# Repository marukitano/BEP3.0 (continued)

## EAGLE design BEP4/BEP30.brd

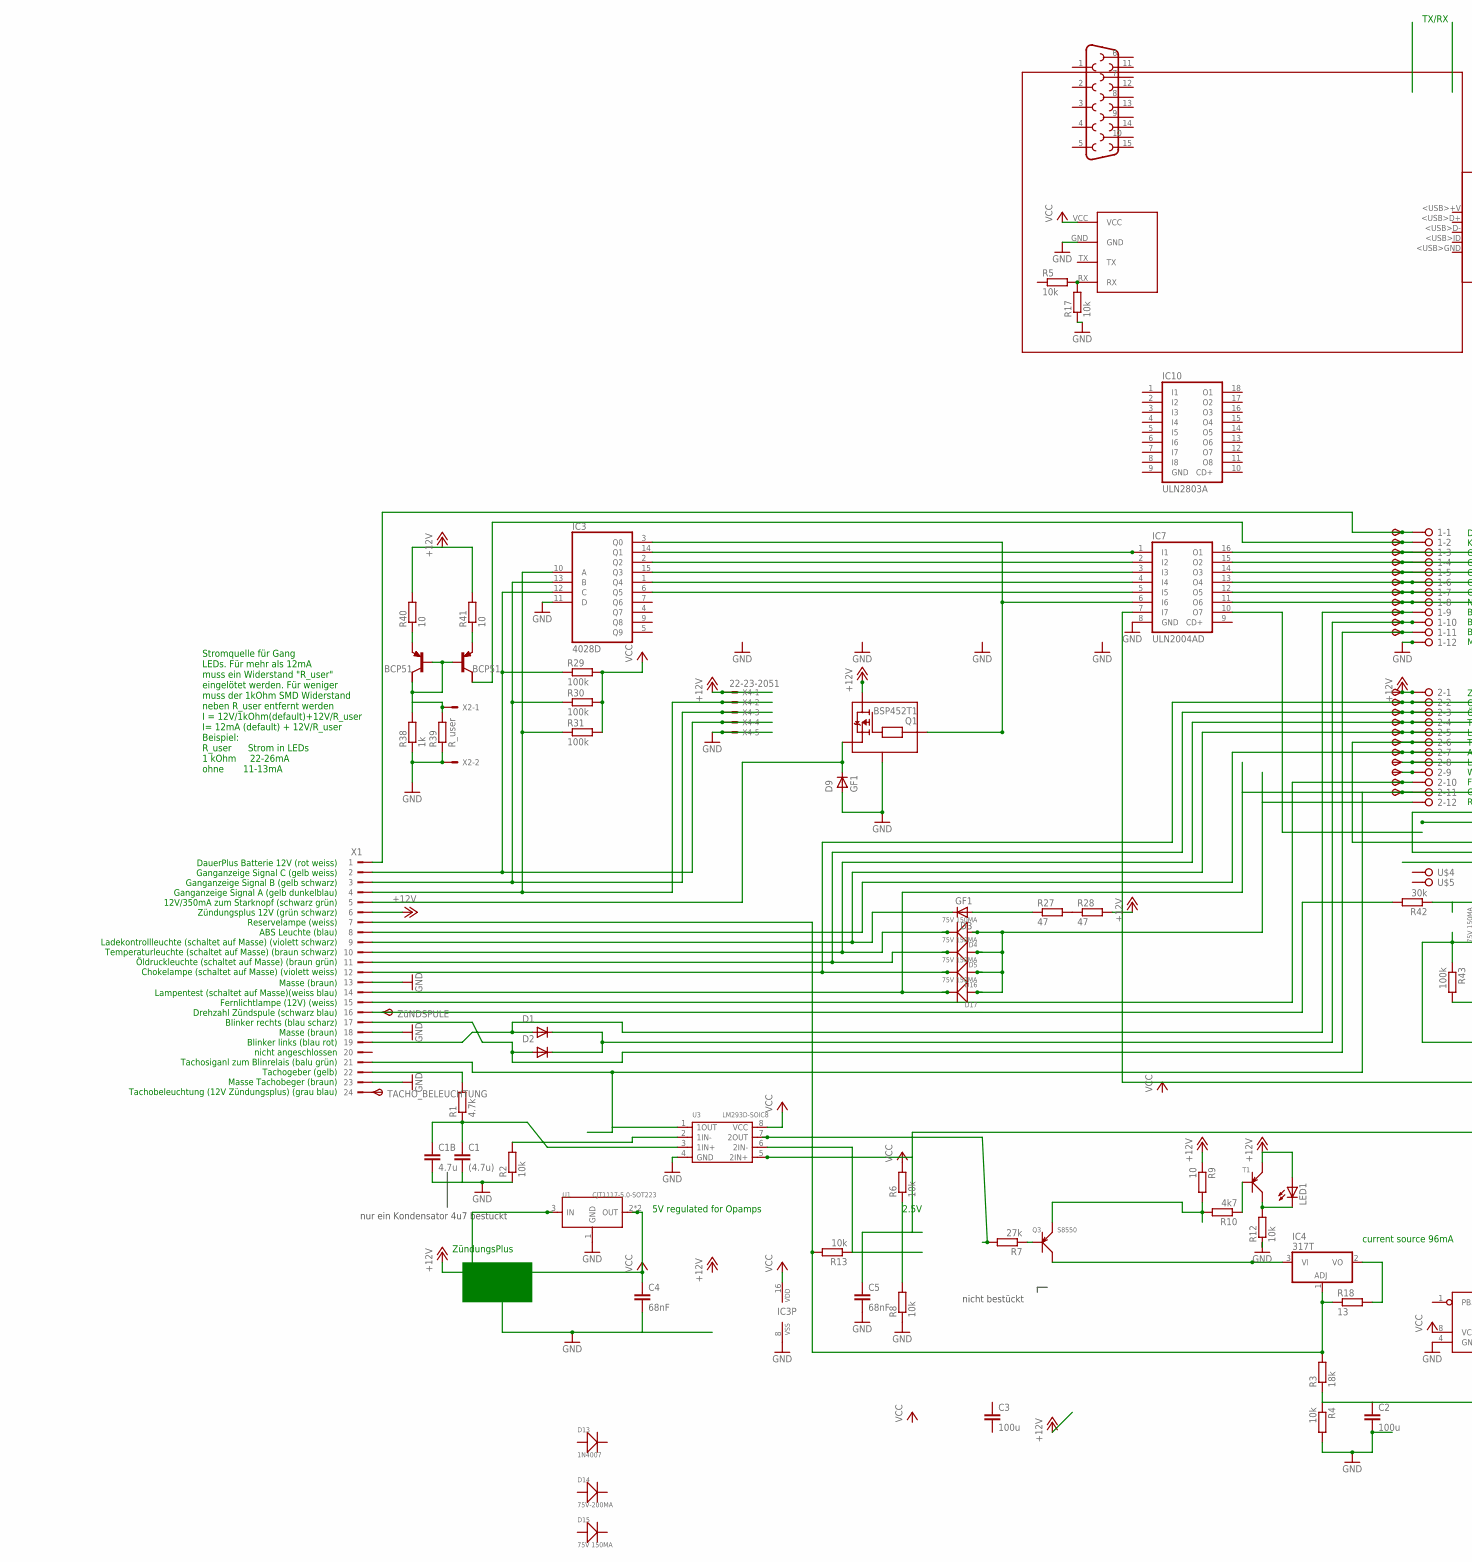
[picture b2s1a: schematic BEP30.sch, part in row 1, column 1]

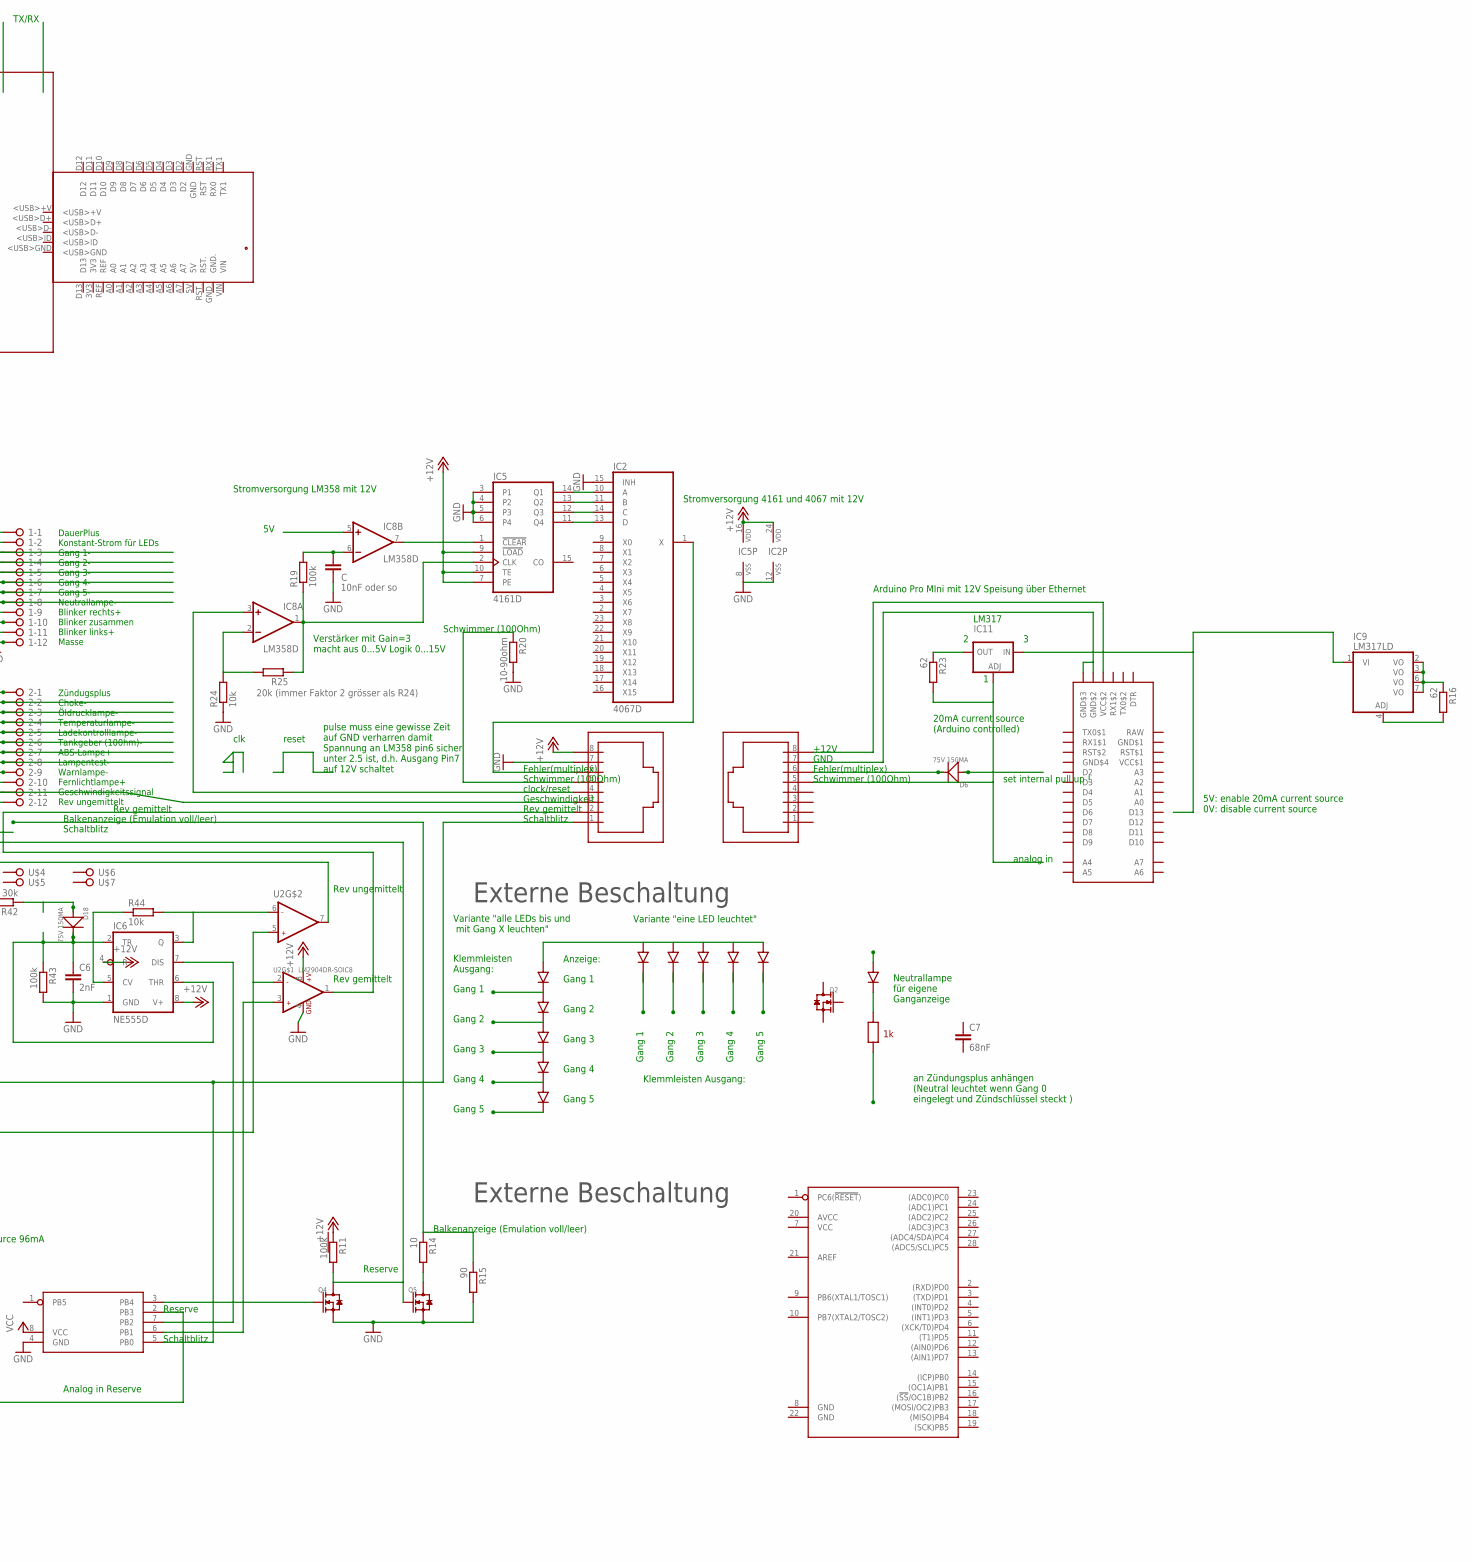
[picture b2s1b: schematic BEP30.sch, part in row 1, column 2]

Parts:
1, 2: 2081-1132; 12-PIN
C: 10nF oder so; C0805K
C1: (4.7u); C1206
C1B: 4.7u; C0805K
C2, C3: 100u; C1206K
C4, C5, C7: 68nF; C1206K
C6: 2nF; C1206K
D1, D2, D3, D9: GF1; SMA-DO214AC
D4, D5, D6, D15, D16, D17, D18: 75V 150MA; LED-1206
D13: 1N4007; DO-214AC
D14: 75V-200MA; LL-34
IC1: ATMEGA328-DIP; DIL28-SLIM
IC2: 4067D; SO24W
IC3: 4028D; SO16
IC4: 317T; TO220H
IC5: 4161D; SO16
IC6: NE555D; SO08
IC7: ULN2004AD; SO16
IC8: LM358D; SO08
IC9: LM317LD; SO08
IC10: ULN2803A; SOP18
IC11: LM317TS; 317TS
J1, J2: RJ45-TE
J_BT_BOARD_1: BLUETOOTH_BOARD; BT_BOARD_FOOTPRINT
LED1: LED3MM
PCB1: ARDUINO_NANO
Q1: BSP452T1; SOT223
Q2, Q4, Q5: SMD-MOSFET-N-CH-50V-200MA-BSS138W-7-F(SOT-23); SOT-23
Q3: S8550; SOT-23
R1: 4.7k; R0805
R2, R4, R5, R6, R8, R12, R13, R17, R24, R44: 10k; R0805
R3: 18k; R0805
R7: 27k; R0805
R9, R14, R40, R41: 10; R0805
R10: 4k7; R0805
R11, R19, R29, R30, R31, R43: 100k; R0805
R15: 90; R0805
R16, R23: 62; R0805
R18: 13; R1206
R20: 10-90ohm; R0805
R25: 20k (immer Faktor 2 grösser als R24); R0805
R27, R28: 47; V235/17
R38: 1k; R0805
R39: R_user; R0805
R42: 30k; R0805
T1: SMD-TRANSISTORS-PNP-25V-500MA-S8550(SOT-23); SOT-23
T13, T14: BCP53T1; SOT223
TACHO_BELEUCHTUNG: TPSP1_1MM; P1_1.0MM
TP1, TP2, TP3, TP4, TP5, TP6, TP7, TP8, TP9, TP10, TP11, TP12, TP16, TP17, TP18, TP19, TP21, TP22, TP23, TP24, TP25, TP26: TPSB1,27; B1,27
U1: CJT1117-5.0-SOT223; SOT-223
U2: LM2904DR-SOIC8; SOIC8-1.27-5X4MM
U3: LM293D-SOIC8; SOIC8-1.27-5X4MM
U$1: TINY85P; DIL08
U$2: DB15
U$3: ARDUINO_PRO_MINI
U$4, U$5, U$6, U$7: 2081-1121; 1-PIN
X1: CON_BMW; 24-PIN
X2: 22-23-2021
X4: 22-23-2051
ZüNDSPULE: TPSP1_1MM; P1_1.0MM

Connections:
+12V: 2.1, IC2.24 (VDD), IC5.7 (PE), IC5.9 (!LOAD), IC5.10 (TE), IC5.16 (VDD), IC6.4 (R), IC6.8 (V+), J1.8, LED1.A, Q1.4 (V+), R9.1, R11.1, R28.2, R40.2, R41.2, T1.2 (E), TP12.TP, U1.3 (IN), U2.8 (+V), X1.6, X4.1
AVCC: IC1.20 (AVCC)
GND: 1.12, C.1, C1.2, C1B.2, C2.2, C4.2, C5.2, C6.2, D9.A, IC1.8 (GND), IC1.22 (GND), IC2.12 (VSS), IC2.15 (INH), IC3.8 (VSS), IC3.11 (D), IC5.3 (P1), IC5.4 (P2), IC5.5 (P3), IC5.6 (P4), IC5.8 (VSS), IC6.1 (GND), IC7.8 (GND), IC10.9 (GND), J1.7, J_BT_BOARD_1.GND, Q1.2 (GND), Q4.2 (S), Q5.2 (S), R2.1, R4.2, R8.1, R12.1, R15.2, R17.1, R20.2, R24.1, R38.1, R39.1, R43.2, U1.1 (GND), U2.4 (GND), U3.4 (GND), U$1.4 (GND), X1.13, X1.18, X1.23, X2.2, X4.5
GND$1: U$3.GDN$1 (GND$1)
GND$4: U$3.GND$4
unnamed: 2.12, D4.+, D5.+, D16.+, D17.+
unnamed: IC3.10 (A), R31.1, X1.4, X4.2
unnamed: IC3.13 (B), R30.1, X1.3, X4.3
unnamed: 2.7, TP22.TP, X1.8
unnamed: IC3.3 (Q0), IC7.6 (I6), Q1.3 (IN)
unnamed: IC3.2 (Q2), IC7.2 (I2)
unnamed: R27.2, R28.1
unnamed: IC4.3 (VI), Q3.3 (C)
unnamed: R13.1, U3.6 (2IN-)
unnamed: D9.K (C), Q1.1 (OUT), X1.5
unnamed: 2.2, D16.-, TP16.TP, X1.12
unnamed: 2.3, D5.-, TP17.TP, X1.11
unnamed: 2.4, D4.-, TP18.TP, X1.10
unnamed: IC4.1 (ADJ), R3.2, R13.2, R18.1, X1.7
unnamed: Q4.1 (G), U$1.3 (PB4)
unnamed: IC3.12 (C), R29.1, X1.2, X4.4
unnamed: 1.5, IC7.14 (O3), TP5.TP
unnamed: D6.-, J2.6
unnamed: 1.9, D1.A, TP9.TP, X1.19
unnamed: 1.11, D2.A, TP11.TP, X1.17
unnamed: 1.10, D1.K (C), D2.K (C), TP10.TP
unnamed: R1.2, X1.22
unnamed: C1.1, C1B.1, R1.1, U3.3 (1IN+)
unnamed: R2.2, U3.2 (1IN-)
unnamed: U3.1 (1OUT), X1.21
unnamed: 1.6, IC7.13 (O4), TP6.TP
unnamed: C2.1, R3.1, R4.1, U$1.2 (PB3)
unnamed: IC4.2 (VO), R18.2
unnamed: C5.1, R6.1, R8.2, U2.2 (-IN1), U2.5 (+IN2), U3.5 (2IN+)
unnamed: R10.1, T1.1 (B)
unnamed: R7.2, U3.7 (2OUT)
unnamed: Q3.1 (B), R7.1
unnamed: J_BT_BOARD_1.RX, R5.2, R17.2
unnamed: IC6.7 (DIS), U$1.7 (PB2)
unnamed: IC3.14 (Q1), IC7.1 (I1)
unnamed: IC3.15 (Q3), IC7.3 (I3)
unnamed: U2.3 (+IN1), U$1.6 (PB1)
unnamed: R14.1, R15.1
unnamed: R42.2, X1.16, ZüNDSPULE.TP
unnamed: IC7.7 (I7), J1.1, U$1.5 (PB0)
unnamed: Q3.2 (E), R9.2, R10.2
unnamed: LED1.K (C), R12.2, T1.3 (C)
unnamed: J1.2, U2.1 (OUT1)
unnamed: Q5.3 (D), R14.2
unnamed: IC3.1 (Q4), IC7.4 (I4)
unnamed: 1.7, IC7.12 (O5), TP7.TP
unnamed: 1.8, IC7.11 (O6), TP8.TP
unnamed: 2.10, TP25.TP, X1.15
unnamed: D3.A, R27.1
unnamed: 2.5, D3.K (C), TP19.TP, X1.9
unnamed: J1.5, R20.1
unnamed: IC2.10 (A), IC5.14 (Q1)
unnamed: TACHO_BELEUCHTUNG.TP, X1.24
unnamed: 1.2, T14.2 (C), TP2.TP
unnamed: 2.6, Q4.3 (D), Q5.1 (G), R11.2, TP21.TP
unnamed: IC9.2 (VO), IC9.3 (VO), IC9.6 (VO), IC9.7 (VO), R16.1
unnamed: IC3.6 (Q5), IC7.5 (I5)
unnamed: IC2.11 (B), IC5.13 (Q2)
unnamed: IC2.14 (C), IC5.12 (Q3)
unnamed: 1.4, IC7.15 (O2), TP4.TP
unnamed: 1.3, IC7.16 (O1), TP3.TP
unnamed: R38.2, R39.2, T13.1 (B), T13.2 (C), T14.1 (B), X2.1
unnamed: 1.1, TP1.TP, X1.1
unnamed: R40.1, T13.3 (E)
unnamed: R41.1, T14.3 (E)
unnamed: D18.+, R42.1
unnamed: IC6.3 (Q), R44.2, U2.6 (-IN2)
unnamed: IC6.5 (CV), R44.1
unnamed: IC2.13 (D), IC5.11 (Q4)
unnamed: IC8.3 (+IN), J1.4
unnamed: C.2, IC8.6 (-IN), R19.2
unnamed: C6.1, D18.-, IC6.2 (TR), IC6.6 (THR), R43.1
unnamed: IC2.1 (X), J1.6
unnamed: 2.11, D17.-, J1.3, TP26.TP, X1.14
unnamed: 2.9, TP24.TP
unnamed: 2.8, TP23.TP
unnamed: IC11.1 (ADJ), J2.5, R23.2
unnamed: IC5.1 (!CLEAR), IC8.7 (OUT)
unnamed: IC9.1 (VI), IC11.3 (IN)
unnamed: J2.8, U$3.VCC$2
unnamed: IC5.2 (CLK), IC8.1 (OUT), R19.1, R25.1
unnamed: J2.7, U$3.GND$2, U$3.GND$3
unnamed: IC9.4 (ADJ), R16.2
unnamed: IC11.2 (OUT), R23.1
unnamed: IC8.2 (-IN), R24.2, R25.2
RAW: U$3.RAW
V+: IC8.8 (V+)
V-: IC8.4 (V-)
VCC: C4.1, IC1.7 (VCC), IC3.16 (VDD), J_BT_BOARD_1.VCC, R6.2, R29.2, R30.2, R31.2, U1.2 (OUT), U1.TER (OUT), U3.8 (VCC), U$1.8 (VCC)
VCC$1: U$3.VCC$1

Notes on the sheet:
5V regulated for Opamps
current source 96mA
ZündungsPlus
Zündugsplus Choke- Öldrucklampe- Temperaturlampe- Ladekontrolllampe- Tankgeber (100hm)- ABS-Lampe+ Lampentest- Warnlampe- Fernlichtlampe+ Geschwindigkeitssignal Rev ungemittelt
DauerPlus Konstant-Strom für LEDs Gang 1- Gang 2- Gang 3- Gang 4- Gang 5- Neutrallampe- Blinker rechts+ Blinker zusammen Blinker links+ Masse
DauerPlus Batterie 12V (rot weiss) Ganganzeige Signal C (gelb weiss) Ganganzeige Signal B (gelb schwarz) Ganganzeige Signal A (gelb dunkelblau) 12V/350mA zum Starknopf (schwarz grün) Zündungsplus 12V (grün schwarz) Reservelampe (weiss) ABS Leuchte (blau) Ladekontrollleuchte (schaltet auf Masse) (vi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
Masse (braun) Lampentest (schaltet auf Masse)(weiss blau) Fernlichtlampe (12V) (weiss) Drehzahl Zündspule (schwarz blau) Blinker rechts (blau scharz) Masse (braun) Blinker links (blau rot) nicht angeschlossen Tachosiganl zum Blinrelais (balu grün) Tachogeber (gelb) Masse Tachobeger (braun) Tachobel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
2.5V
Stromquelle für Gang LEDs. Für mehr als 12mA muss ein Widerstand "R_user" eingelötet werden. Für weniger muss der 1kOhm SMD Widerstand neben R_user entfernt werden I = 12V/1kOhm(default)+12V/R_user I= 12mA (default) + 12V/R_user Beispiel: R_user Strom in LEDs 1 kOhm 22-26mA ohne 11-13mA
Gang 1
Gang 2
Gang 3
Gang 4
Gang 5
Variante "eine LED leuchtet"
Variante "alle LEDs bis und mit Gang X leuchten"
Klemmleisten Ausgang:
Klemmleisten Ausgang:
an Zündungsplus anhängen (Neutral leuchtet wenn Gang 0 eingelegt und Zündschlüssel steckt )
Rev ungemittelt
Neutrallampe für eigene Ganganzeige
Externe Beschaltung
Anzeige:
nicht bestückt
nur ein Kondensator 4u7 bestückt
Rev gemittelt
Schaltblitz
Analog in Reserve
Reserve
Balkenanzeige (Emulation voll/leer)
Schwimmer (100Ohm)
20mA current source (Arduino controlled)
TX/RX
5V: enable 20mA current source 0V: disable current source
Geschwindigkeit
clock/reset
Fehler(multiplex)
Stromversorgung 4161 und 4067 mit 12V
Stromversorgung LM358 mit 12V
Arduino Pro MIni mit 12V Speisung über Ethernet

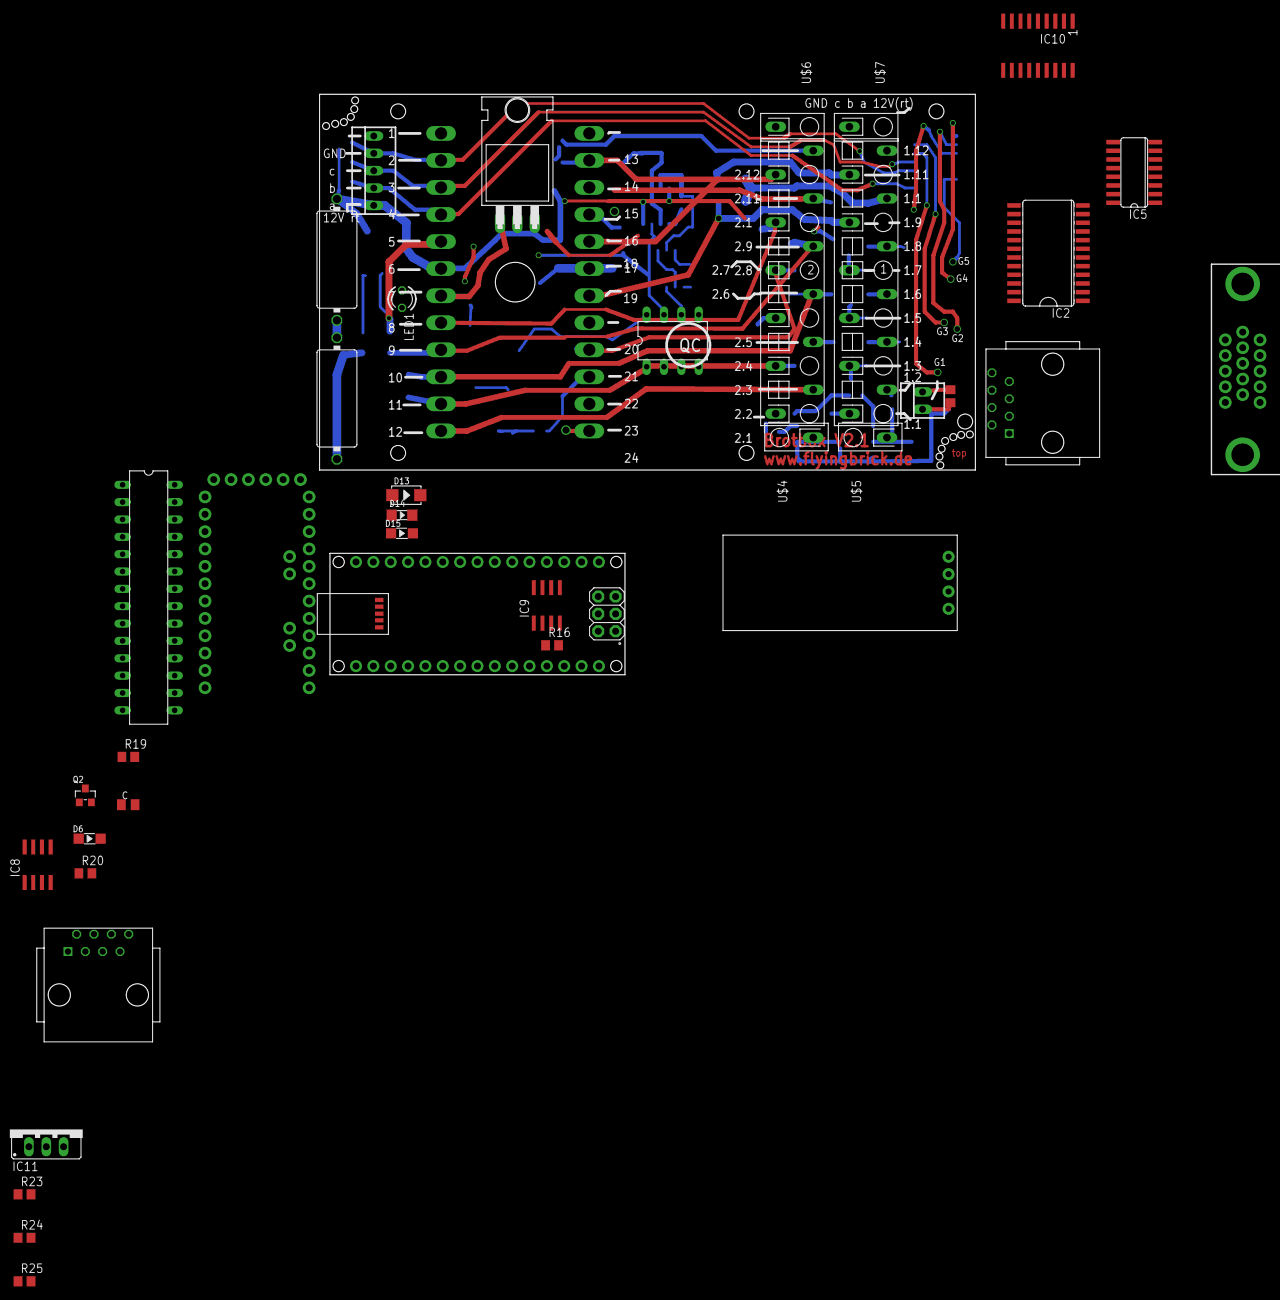
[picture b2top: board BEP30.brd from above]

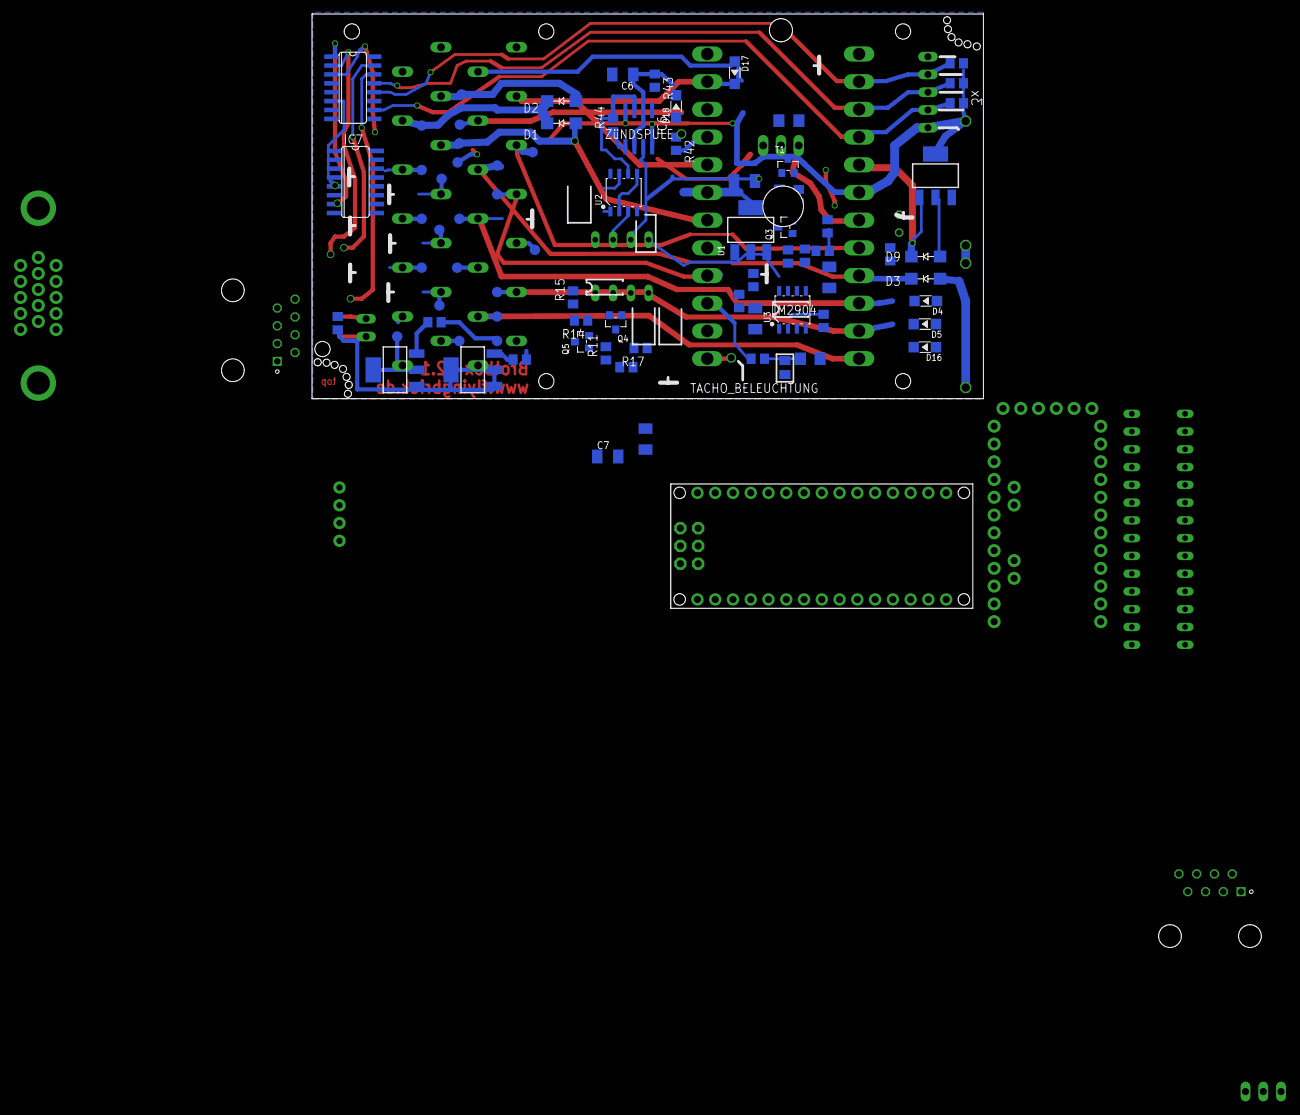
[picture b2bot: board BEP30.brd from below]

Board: 2 copper layers, 96.0 x 85.0 mm, 120 parts (80 on the bottom side), 88 nets.

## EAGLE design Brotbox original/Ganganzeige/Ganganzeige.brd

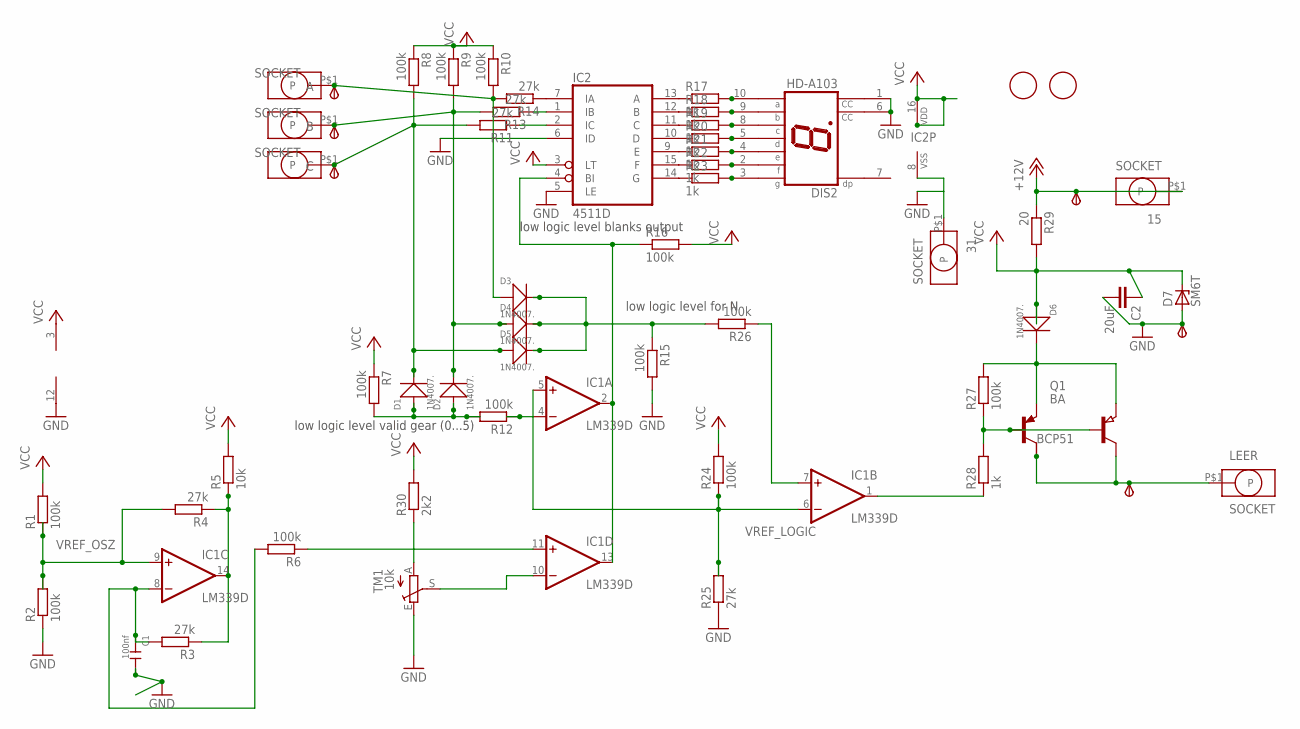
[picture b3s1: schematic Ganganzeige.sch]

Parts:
15, 31: SOCKET; ID2.5MM
15_: TPSB2.0; B2.0
A: SOCKET; ID2.5MM
A_: TPSB2.0; B2.0
B: SOCKET; ID2.5MM
B_: TPSB2.0; B2.0
C: SOCKET; ID2.5MM
C1: 100nf; C0805
C2: 20uF; C1206K
C_: TPSB2.0; B2.0
D1, D2, D3, D4, D5, D6: 1N4007.; DO-214AC
D7: SM6T; DO214AA
DIS2: HD-A103; HDSP-A
FID1, FID2: FIDUCIAL; FIDUCIAL_1MM
GND_: TPSB2.0; B2.0
IC1: LM339D; SO14
IC2: 4511D; SO16
LEER: SOCKET; ID2.5MM
LEER_: TPSB2.0; B2.0
Q1: BA; SOT89
R1, R2, R6, R7, R8, R9, R10, R12, R15, R16, R24, R26, R27: 100k; R0805
R3, R4, R11, R13, R14, R25: 27k; R0805
R5: 10k; R0805
R17, R18, R19, R20, R21, R22, R23, R28: 1k; R0805
R29: 20; R1206
R30: 2k2; R0805
T: BCP53T1; SOT223
TM1: 10k; S63X

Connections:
+12V: 15.P$1, 15_.TP, R29.1
GND: 31.P$1, C1.2, C2.2, D7.A, DIS2.1 (CC), DIS2.6 (CC), GND_.TP, IC1.12 (GND), IC2.5 (LE), IC2.6 (ID), IC2.8 (VSS), R2.1, R15.2, R25.1, TM1.E
unnamed: IC2.13 (A), R17.1
unnamed: DIS2.10 (A), R17.2
unnamed: IC2.12 (B), R18.1
unnamed: DIS2.9 (B), R18.2
unnamed: IC2.11 (C), R19.1
unnamed: DIS2.8 (C), R19.2
unnamed: IC2.10 (D), R20.1
unnamed: DIS2.5 (D), R20.2
unnamed: IC2.9 (E), R21.1
unnamed: R30.1, TM1.A
unnamed: DIS2.4 (E), R21.2
unnamed: IC2.15 (F), R22.1
unnamed: DIS2.2 (F), R22.2
unnamed: IC2.14 (G), R23.1
unnamed: DIS2.3 (G), R23.2
unnamed: A.P$1, A_.TP, D3.1 (+), R10.2, R14.2
unnamed: B.P$1, B_.TP, D2.2 (-), D4.1 (+), R9.2, R13.2
unnamed: C.P$1, C_.TP, D1.2 (-), D5.1 (+), R8.2, R11.2
unnamed: IC1.1 (OUT), R28.1
unnamed: Q1.1 (B), R27.1, R28.2, T.1 (B)
unnamed: C1.1, IC1.8 (-IN), R3.2, R6.2
unnamed: IC1.14 (OUT), R3.1, R4.1, R5.1
unnamed: D1.1 (+), D2.1 (+), R7.2, R12.2
unnamed: IC1.2 (OUT), IC1.13 (OUT), IC2.4 (BI), R16.1
unnamed: IC1.11 (+IN), R6.1
unnamed: IC1.10 (-IN), TM1.S
unnamed: IC1.7 (+IN), R26.1
unnamed: IC1.4 (-IN), R12.1
unnamed: IC2.7 (IA), R14.1
unnamed: D3.2 (-), D4.2 (-), D5.2 (-), R15.1, R26.2
unnamed: IC2.2 (IC), R11.1
unnamed: IC2.1 (IB), R13.1
VCC: C2.1, D6.1 (+), D7.C, IC1.3 (V+), IC2.3 (LT), IC2.16 (VDD), R1.2, R5.2, R7.1, R8.1, R9.1, R10.1, R16.2, R24.2, R29.2, R30.2
VREF_LOGIC: IC1.5 (+IN), IC1.6 (-IN), R24.1, R25.2
VREF_OSZ: IC1.9 (+IN), R1.1, R2.2, R4.2
ZUENDPLUS_OUT: LEER.P$1, LEER_.TP, Q1.2 (C), T.2 (C)
ZUEND_EIN: D6.2 (-), Q1.3 (E), R27.2, T.3 (E)

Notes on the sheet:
low logic level for N
low logic level valid gear (0...5)
low logic level blanks output

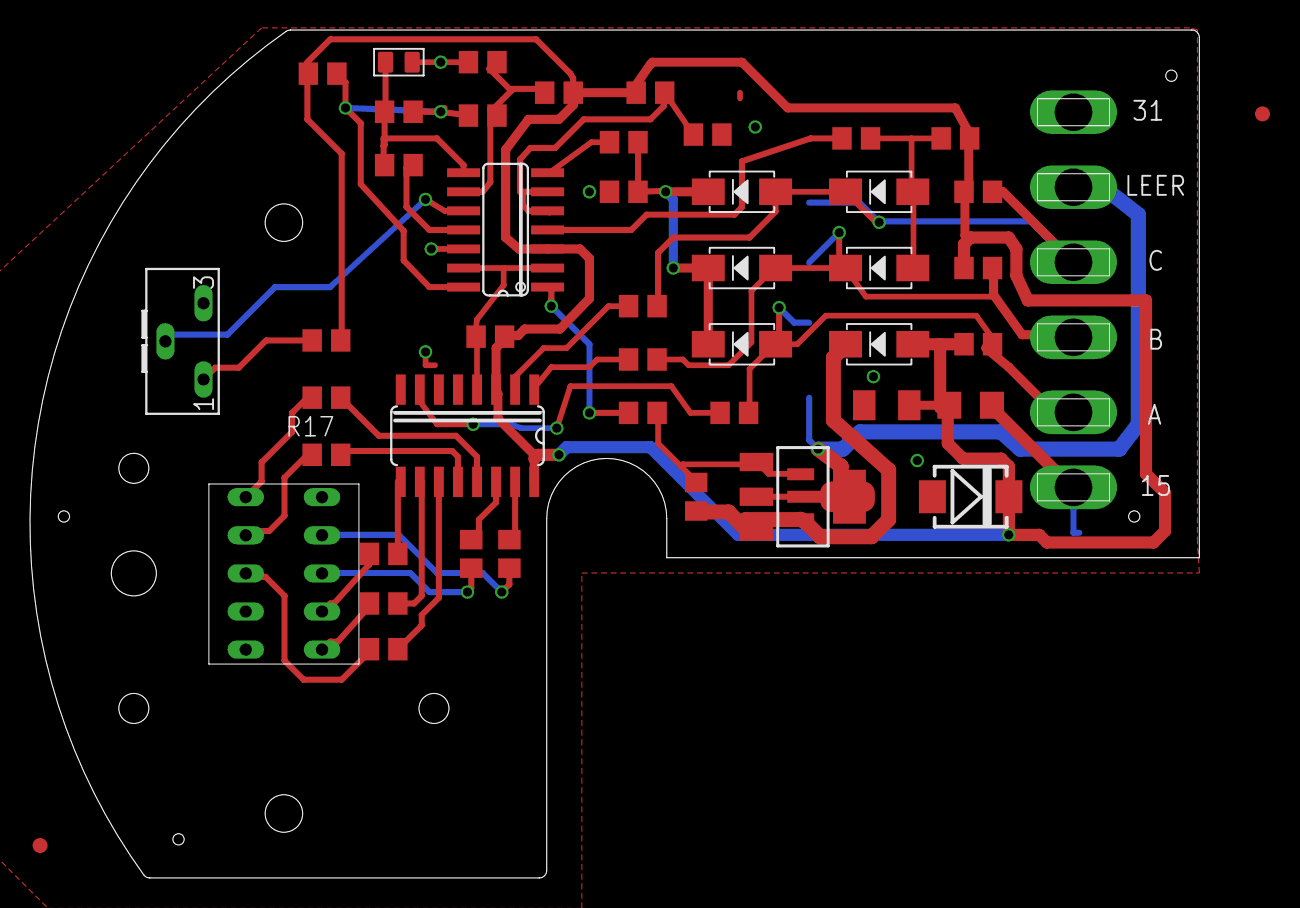
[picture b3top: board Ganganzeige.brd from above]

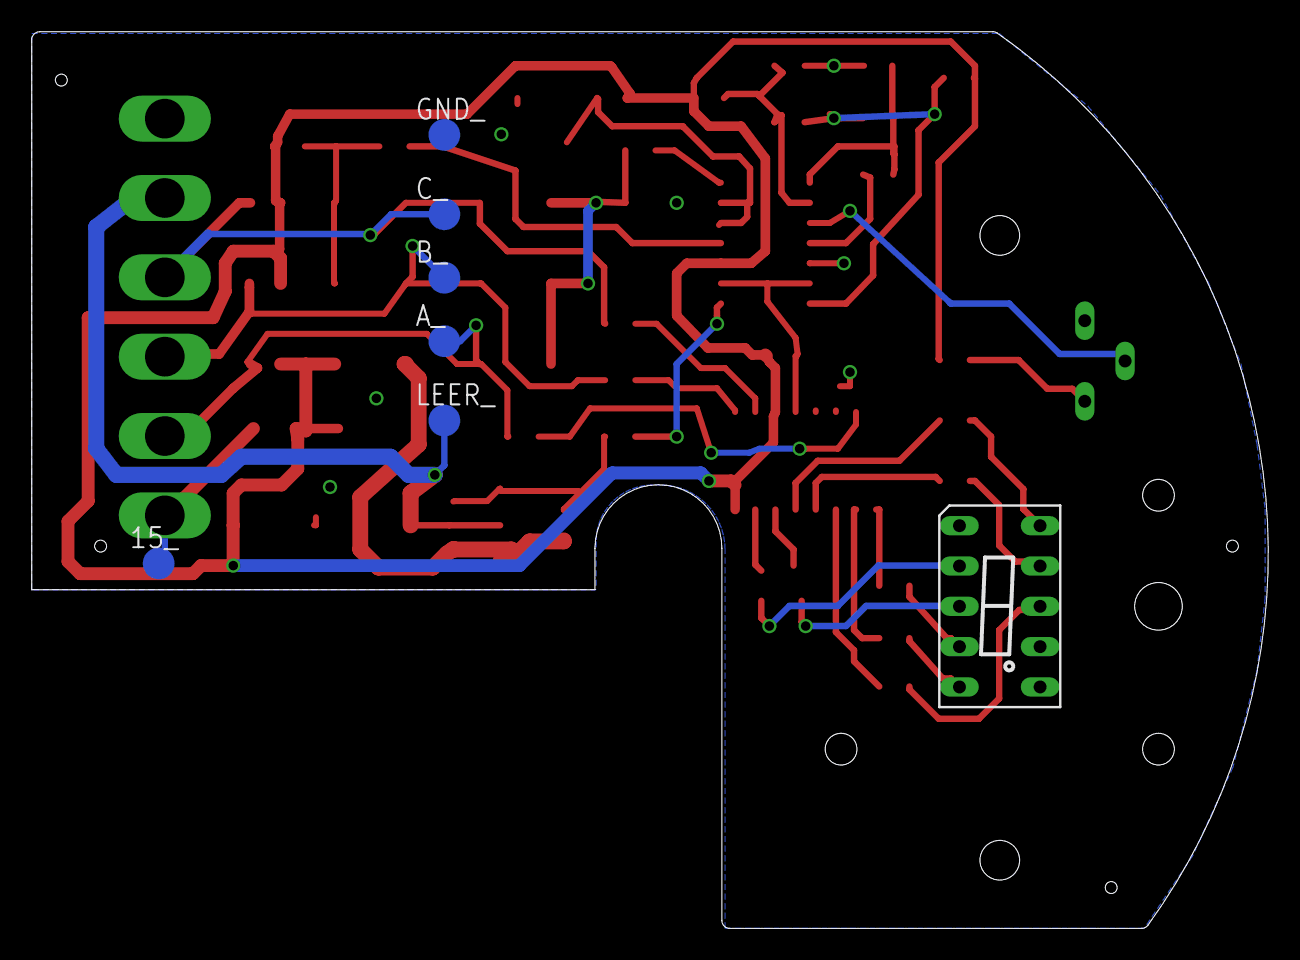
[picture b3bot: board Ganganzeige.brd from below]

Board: 2 copper layers, 77.9 x 56.5 mm, 59 parts (7 on the bottom side), 39 nets.

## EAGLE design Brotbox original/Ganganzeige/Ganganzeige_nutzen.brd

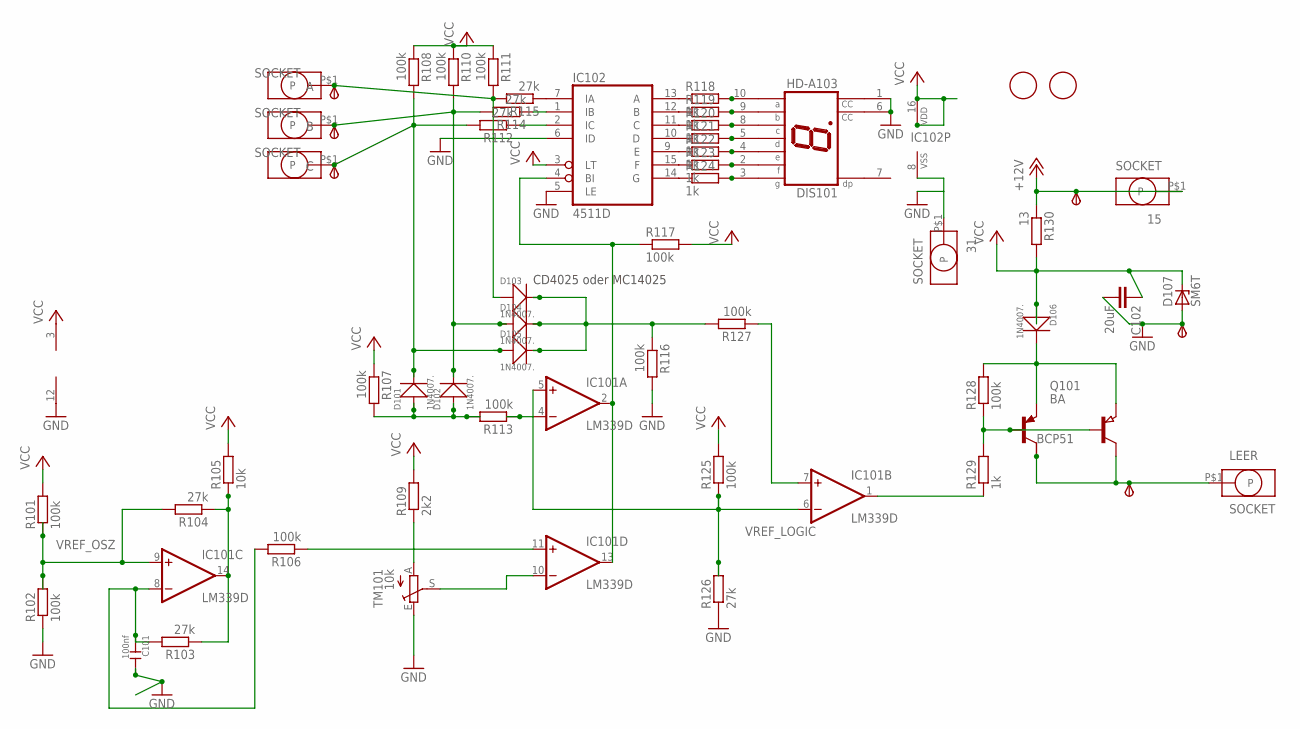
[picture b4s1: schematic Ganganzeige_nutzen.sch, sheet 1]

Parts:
15, 31: SOCKET; ID2.5MM
15_: TPSB2.0; B2.0
A: SOCKET; ID2.5MM
A_: TPSB2.0; B2.0
B: SOCKET; ID2.5MM
B_: TPSB2.0; B2.0
C: SOCKET; ID2.5MM
C101: 100nf; C0805
C102: 20uF; C1206K
C_: TPSB2.0; B2.0
D101, D102, D103, D104, D105, D106: 1N4007.; DO-214AC
D107: SM6T; DO214AA
DIS101: HD-A103; HDSP-A
FID101, FID102: FIDUCIAL; FIDUCIAL_1MM
GND_: TPSB2.0; B2.0
IC101: LM339D; SO14
IC102: 4511D; SO16
LEER: SOCKET; ID2.5MM
LEER_: TPSB2.0; B2.0
Q101: BA; SOT89
R101, R102, R106, R107, R108, R110, R111, R113, R116, R117, R125, R127, R128: 100k; R0805
R103, R104, R112, R114, R115, R126: 27k; R0805
R105: 10k; R0805
R109: 2k2; R0805
R118, R119, R120, R121, R122, R123, R124, R129: 1k; R0805
R130: 13; R1206
T: BCP53T1; SOT223
TM101: 10k; S63X

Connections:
+12V: 15.P$1, 15_.TP, R130.1; also elsewhere on the board
GND: 31.P$1, C101.2, C102.2, D107.A, DIS101.1 (CC), DIS101.6 (CC), GND_.TP, IC101.12 (GND), IC102.5 (LE), IC102.6 (ID), IC102.8 (VSS), R102.1, R116.2, R126.1, TM101.E; also elsewhere on the board
unnamed: IC102.13 (A), R118.1
unnamed: DIS101.10 (A), R118.2
unnamed: IC102.12 (B), R119.1
unnamed: DIS101.9 (B), R119.2
unnamed: IC102.11 (C), R120.1
unnamed: DIS101.8 (C), R120.2
unnamed: IC102.10 (D), R121.1
unnamed: DIS101.5 (D), R121.2
unnamed: IC102.9 (E), R122.1
unnamed: R109.1, TM101.A
unnamed: DIS101.4 (E), R122.2
unnamed: IC102.15 (F), R123.1
unnamed: DIS101.2 (F), R123.2
unnamed: IC102.14 (G), R124.1
unnamed: DIS101.3 (G), R124.2
unnamed: A.P$1, A_.TP, D103.1 (+), R111.2, R115.2
unnamed: B.P$1, B_.TP, D102.2 (-), D104.1 (+), R110.2, R114.2
unnamed: C.P$1, C_.TP, D101.2 (-), D105.1 (+), R108.2, R112.2
unnamed: IC101.1 (OUT), R129.1
unnamed: Q101.1 (B), R128.1, R129.2, T.1 (B)
unnamed: C101.1, IC101.8 (-IN), R103.2, R106.2
unnamed: IC101.14 (OUT), R103.1, R104.1, R105.1
unnamed: D101.1 (+), D102.1 (+), R107.2, R113.2
unnamed: IC101.2 (OUT), IC101.13 (OUT), IC102.4 (BI), R117.1
unnamed: IC101.11 (+IN), R106.1
unnamed: IC101.10 (-IN), TM101.S
unnamed: IC101.7 (+IN), R127.1
unnamed: IC101.4 (-IN), R113.1
unnamed: IC102.7 (IA), R115.1
unnamed: D103.2 (-), D104.2 (-), D105.2 (-), R116.1, R127.2
unnamed: IC102.2 (IC), R112.1
unnamed: IC102.1 (IB), R114.1
VCC: C102.1, D106.1 (+), D107.C, IC101.3 (V+), IC102.3 (LT), IC102.16 (VDD), R101.2, R105.2, R107.1, R108.1, R109.2, R110.1, R111.1, R117.2, R125.2, R130.2; also elsewhere on the board
VREF_LOGIC: IC101.5 (+IN), IC101.6 (-IN), R125.1, R126.2; also elsewhere on the board
VREF_OSZ: IC101.9 (+IN), R101.1, R102.2, R104.2; also elsewhere on the board
ZUENDPLUS_OUT: LEER.P$1, LEER_.TP, Q101.2 (C), T.2 (C)
ZUEND_EIN: D106.2 (-), Q101.3 (E), R128.2, T.3 (E)

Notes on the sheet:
CD4025 oder MC14025

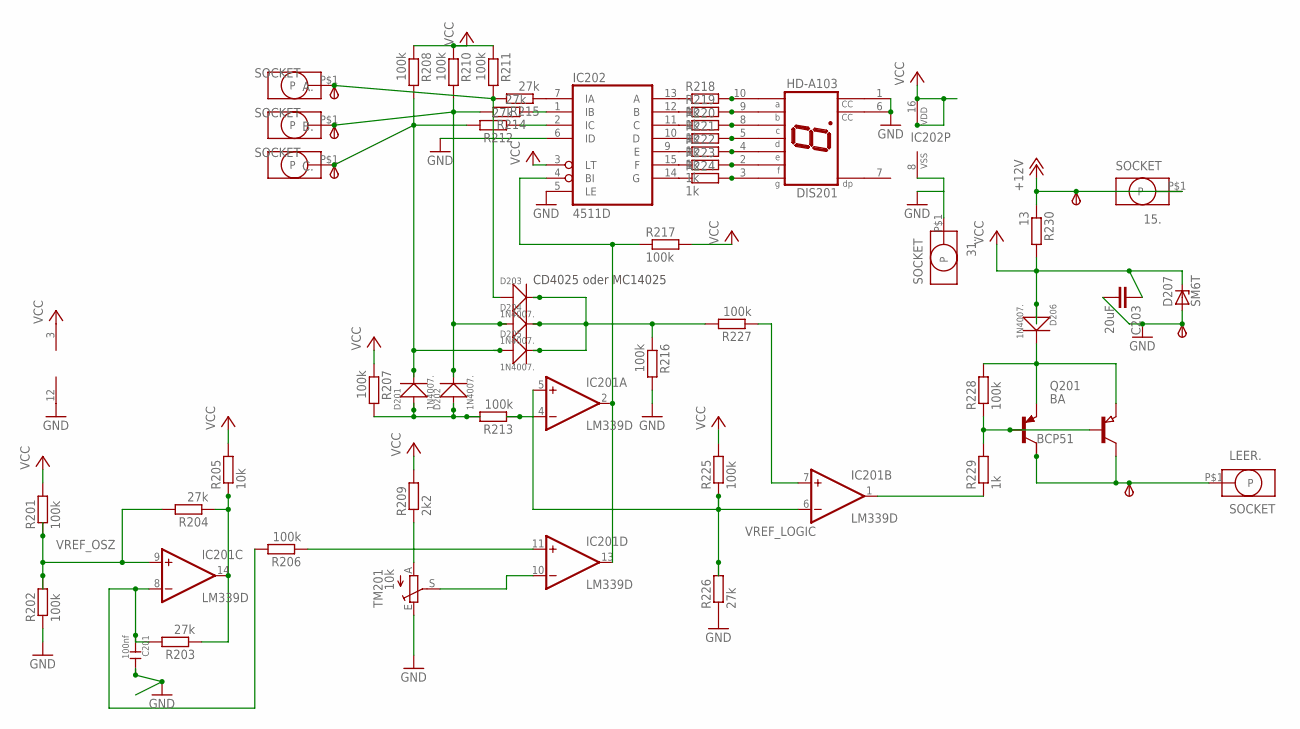
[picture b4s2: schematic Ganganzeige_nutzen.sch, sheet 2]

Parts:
15., 31.: SOCKET; ID2.5MM
15_201: TPSB2.0; B2.0
A.: SOCKET; ID2.5MM
A_201: TPSB2.0; B2.0
B.: SOCKET; ID2.5MM
B_201: TPSB2.0; B2.0
C201: 100nf; C0805
C203: 20uF; C1206K
C.: SOCKET; ID2.5MM
C_201: TPSB2.0; B2.0
D201, D202, D203, D204, D205, D206: 1N4007.; DO-214AC
D207: SM6T; DO214AA
DIS201: HD-A103; HDSP-A
GND_201: TPSB2.0; B2.0
IC201: LM339D; SO14
IC202: 4511D; SO16
LEER.: SOCKET; ID2.5MM
LEER_201: TPSB2.0; B2.0
Q201: BA; SOT89
R201, R202, R206, R207, R208, R210, R211, R213, R216, R217, R225, R227, R228: 100k; R0805
R203, R204, R212, R214, R215, R226: 27k; R0805
R205: 10k; R0805
R209: 2k2; R0805
R218, R219, R220, R221, R222, R223, R224, R229: 1k; R0805
R230: 13; R1206
T201: BCP53T1; SOT223
TM201: 10k; S63X

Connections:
+12V: 15..P$1, 15_201.TP, R230.1; also elsewhere on the board
GND: 31..P$1, C201.2, C203.2, D207.A, DIS201.1 (CC), DIS201.6 (CC), GND_201.TP, IC201.12 (GND), IC202.5 (LE), IC202.6 (ID), IC202.8 (VSS), R202.1, R216.2, R226.1, TM201.E; also elsewhere on the board
unnamed: IC202.13 (A), R218.1
unnamed: DIS201.10 (A), R218.2
unnamed: IC202.12 (B), R219.1
unnamed: DIS201.9 (B), R219.2
unnamed: IC202.11 (C), R220.1
unnamed: DIS201.8 (C), R220.2
unnamed: IC202.10 (D), R221.1
unnamed: DIS201.5 (D), R221.2
unnamed: IC202.9 (E), R222.1
unnamed: DIS201.4 (E), R222.2
unnamed: IC202.15 (F), R223.1
unnamed: DIS201.2 (F), R223.2
unnamed: IC202.14 (G), R224.1
unnamed: DIS201.3 (G), R224.2
unnamed: A..P$1, A_201.TP, D203.1 (+), R211.2, R215.2
unnamed: B..P$1, B_201.TP, D202.2 (-), D204.1 (+), R210.2, R214.2
unnamed: C..P$1, C_201.TP, D201.2 (-), D205.1 (+), R208.2, R212.2
unnamed: IC201.1 (OUT), R229.1
unnamed: Q201.1 (B), R228.1, R229.2, T201.1 (B)
unnamed: D201.1 (+), D202.1 (+), R207.2, R213.2
unnamed: IC201.2 (OUT), IC201.13 (OUT), IC202.4 (BI), R217.1
unnamed: D203.2 (-), D204.2 (-), D205.2 (-), R216.1, R227.2
unnamed: C201.1, IC201.8 (-IN), R203.2, R206.2
unnamed: IC201.14 (OUT), R203.1, R204.1, R205.1
unnamed: IC201.10 (-IN), TM201.S
unnamed: IC201.11 (+IN), R206.1
unnamed: IC201.7 (+IN), R227.1
unnamed: IC201.4 (-IN), R213.1
unnamed: IC202.7 (IA), R215.1
unnamed: IC202.2 (IC), R212.1
unnamed: IC202.1 (IB), R214.1
unnamed: R209.1, TM201.A
VCC: C203.1, D206.1 (+), D207.C, IC201.3 (V+), IC202.3 (LT), IC202.16 (VDD), R201.2, R205.2, R207.1, R208.1, R209.2, R210.1, R211.1, R217.2, R225.2, R230.2; also elsewhere on the board
VREF_LOGIC: IC201.5 (+IN), IC201.6 (-IN), R225.1, R226.2; also elsewhere on the board
VREF_OSZ: IC201.9 (+IN), R201.1, R202.2, R204.2; also elsewhere on the board
ZUENDPLUS_OUT1: LEER..P$1, LEER_201.TP, Q201.2 (C), T201.2 (C)
ZUEND_EIN1: D206.2 (-), Q201.3 (E), R228.2, T201.3 (E)

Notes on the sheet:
CD4025 oder MC14025
